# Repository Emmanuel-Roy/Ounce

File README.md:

# Ounce

Play your Nintendo Switch from anywhere. Four Picos each appear to the Switch as
a real Switch Pro Controller, a fifth drives them over SPI, and a Windows client
turns your keyboard and USB pads into those four players while showing the
Switch's video in the same window.

```
keyboard / pads -> Windows client -> USB serial -> Pico 2 W master
                                                        |  SPI
                                          +------+------+------+------+
                                        Pico   Pico   Pico   Pico   -> Switch USB
                                       player1 player2 player3 player4
```

> **The artwork is AI-generated.** The banner, logo and app icon all came out of
> an image model — this is a hobby project and I could not afford to pay an
> artist for it. Everything in [`Ounce-Client/Graphics/`](Ounce-Client/Graphics/)
> is that; the photos of the board and the wiring are real. Artists welcome —
> open an issue.

## Parts

| Qty | Part | Purpose |
| --- | --- | --- |
| 1 | **Raspberry Pi Pico 2 W** (RP2350) | Master |
| 4 | **Raspberry Pi Pico 1** (RP2040) | Servants — one per player |
| 5 | Micro-USB cables | 4 for servants -> Switch (powered hub into the dock), 1 for master -> PC (power + serial) |
| 1 | **Elgato capture card** (4K S or similar) | Switch video in the client window |
| 1 | **Ounce PCB** or breadboard + jumpers | SPI bus and common ground |

Capture card is optional — run with `--no-preview` for input only.

## Layout

```
bin/
├── firmware/      OunceMaster.uf2, OunceServant.uf2   <-- flash these
├── client/        OunceClient/ - the app, no Python needed
└── pcb/           Ounce-PCB-fab.zip - gerbers + drill, ready to order
Ounce-Client/      Windows client: test_bridge.py, wiring_test.py, build_exe.bat
└── Graphics/      AI-generated logo, icon and banner - all of it, see its README
Ounce-Hardware/    master-firmware/, servant-firmware/, pcb/, pico-sdk/
```

## Wiring

SCK and MOSI are **shared** by all four servants. CS and MISO are **one per
servant** — an RP2040 slave does not release MISO when deselected, so four on
one wire would fight.

**Master (Pico 2 W)**

| Signal | GPIO | Pin | To |
| --- | --- | --- | --- |
| SCK | GP18 | 24 | SCK on all servants |
| MOSI | GP19 | 25 | MOSI (GP16) on all servants |
| CS 0–3 | GP21, GP22, GP26, GP27 | 27, 29, 31, 32 | CS on servant 0, 1, 2, 3 |
| MISO 0–3 | GP0, GP4, GP16, GP20 | 1, 6, 21, 26 | MISO from servant 0, 1, 2, 3 |
| GND | GND | 38 | GND (pin 38) on every servant |

**Each servant (Pico 1)** — identical for all four:

| Signal | GPIO | Pin | To |
| --- | --- | --- | --- |
| MOSI in | GP16 | 21 | master GP19 |
| CS | GP17 | 22 | that servant's own CS pin |
| SCK | GP18 | 24 | master GP18 |
| MISO out | GP19 | 25 | that servant's own MISO pin |
| GND | GND | 38 | master GND (pin 38) |

**Every board must share a ground with the master** — without it you get
intermittent garbage rather than a clean failure. Bus is 4 MHz, SPI mode 1.
Servants are numbered purely by which CS pin they are wired to, so any Pico
works in any slot.

Breadboard and jumpers work fine — this is the build the firmware was developed
against, and it holds 94–100% packet delivery at 4 MHz:

The PCB is the same eleven nets, tidier.

Verify before going further:

```bash
python Ounce-Client/wiring_test.py            # PASS/FAIL per slot
python Ounce-Client/wiring_test.py --identify # drive one slot at a time
python Ounce-Client/wiring_test.py --map      # slot -> board -> Windows USB device
```

SPI slot order and USB enumeration order are unrelated — slot 2 is just "the
board on CS GP26" and may appear third or fourth in Windows.

## Flashing

Prebuilt images are in `bin/` — no build needed.

| Board | Hold BOOTSEL, plug in, drive appears | Drag on |
| --- | --- | --- |
| Servants (×4) | `RPI-RP2` | `bin/firmware/OunceServant.uf2` |
| Master | `RP2350` | `bin/firmware/OunceMaster.uf2` |

All four servants get the **same** file; each learns its player number from its
CS pin.

The servants ask the Switch to poll them every **1 ms**, not the 8 ms a real Pro
Controller reports — that interval was over half of Ounce's total input latency.
If a servant will not enumerate on the console, that non-standard `bInterval` in
`SwitchProDescriptors.h` is the first thing to put back to `0x08`.

## Building

```bash
git clone --recursive https://github.com/Emmanuel-Roy/Ounce.git
```

Already cloned? `git submodule update --init --recursive`.

**Master firmware** — needs CMake, a make tool and `arm-none-eabi-gcc` (the [Pico
Windows installer](https://www.raspberrypi.com/documentation/microcontrollers/c_sdk.html)
has all three):

```bash
cd Ounce-Hardware/master-firmware
cmake -B build -DPICO_SDK_PATH=../pico-sdk
cmake --build build
```

Add `-G Ninja` or `-G "MinGW Makefiles"` if CMake does not pick a generator on
its own. Output is `build/OunceMaster.uf2`.

**Servant firmware** (`SKIP_WEBBUILD` avoids needing Node/npm for GP2040-CE's
unused web configurator):

```bash
cd Ounce-Hardware/servant-firmware/GP2040-CE-SPI
cmake -B build -DSKIP_WEBBUILD=ON -DPICO_SDK_PATH=../../pico-sdk
cmake --build build
```

Output is `build/OunceServant.uf2`. Both firmwares use the vendored SDK, which
is pinned to **2.2.0** because that is what GP2040-CE builds against — on 2.3.0
the servant fails to link, with mbedtls calling PSA crypto functions that its
config leaves out.

If that build dies in **picotool** rather than in the firmware (`No rule to make
target ...compiler_depend.make` under `enc_bootloader_mbedtls`), the SDK is
building picotool from source and failing at it — seen with the MinGW Makefiles
generator. Point CMake at one that already exists instead:

```bash
cmake -B build -DSKIP_WEBBUILD=ON -DPICO_SDK_PATH=../../pico-sdk \
      -Dpicotool_DIR=<some-existing-build>/_deps/picotool
```

That directory is the one holding `picotoolConfig.cmake`, not `picotool-build/`.

**Client:**

```bash
pip install -r Ounce-Client/requirements.txt
python Ounce-Client/test_bridge.py
```

`python-vlc` is only the binding — also install VLC itself, at the same
bit-width as your Python, or video will not start.

`Ounce-Client\build_exe.bat` rebuilds `bin\client\OunceClient\`. It uses `--onedir`
deliberately: a onefile build relaunches itself as a child process, and Steam
Input only instruments the process Steam launched. Keep the folder together —
the exe needs `_internal\` beside it. The exe icon and the window icon both come
from `Graphics/icon.png` beside it —
[`Ounce-Client/Graphics/README.md`](Ounce-Client/Graphics/README.md) has the
one-liner that regenerates them.

## Running

Run with no arguments and it asks what drives each player:

```text
   1) PS5 Controller     k) Keyboard     d) Disabled

  Controller 1 (slot 0) : 1
  Controller 2 (slot 1) : k
```

Ounce's own servants are filtered out of the list. Only assigned slots are
enabled. To skip the prompt:

```bash
python test_bridge.py --assign all=keyboard
python test_bridge.py --assign 0=pad:DualSense --assign 1,2,3=keyboard
python test_bridge.py --list-controllers
```

`SLOT` is `0`–`3`, a comma list, or `all`; `SOURCE` is `keyboard` or
`pad:<index|name>` (prefer names — indices shift when devices are replugged).

A pad and the keyboard can drive the same player at once. Each player's menu
lists the controllers first, then how much keyboard rides along with it:

| Keyboard | Player gets |
| --- | --- |
| **Full keyboard** | every input, merged with the pad |
| **Home / Capture only** | just those two keys; the rest of the keyboard is ignored |
| **No keyboard** | the pad alone |

**Home / Capture only** is the useful one for a Steam Controller, which has no
Home or Capture button: you get those two without WASD also grabbing the stick
out from under the pad. The keyboard setting belongs to the player rather than
the pad, so changing which controller is assigned keeps it.

On the Switch: **System Settings → Controllers and Sensors → Pro Controller
Wired Communication → ON**.

**Video** — the window opens by default at **1440p60 raw** (`--no-window` for a
headless console bridge). `--list-modes` shows what your card offers,
`--capture-mode 3840x2160` to override. **F11** toggles borderless fullscreen.

1440p raw is the default because it is the highest mode that actually holds 60.
Measured on an RX 9070 XT / Ryzen 7 7700X:

| Mode | Frame rate | Dropped |
| --- | --- | --- |
| 2560×1440@60 nv12 | **59.0 / 60** | 1 |
| 3840×2160@60 mjpeg | 40.6 / 60 | 129 |
| 2560×1440@144 mjpeg | 90.8 / 144 | 386 |

4K60 is MJPEG only — the card caps raw at 4K30 — and MJPEG costs a CPU decode
plus a software colour conversion on every frame. Neither GPU decode nor more
decoder threads helps: AMD and NVIDIA have no MJPEG hardware decoder, and
raising `--avcodec-threads` past 4 makes it worse. Raw skips both steps, so the
frames go straight to the GPU.

A mode must be requested explicitly or DirectShow hands out 640×480. The card's
HDMI passthrough never reaches the PC, so only the capture path can feed the
window.

**Video latency.** If you play off this window rather than off the card's HDMI
passthrough, the picture — not the controller — is what you feel. The input path
is about 1.7 ms end to end, so anything the capture path buffers dwarfs it.

Audio is therefore split out of VLC by default, and `--capture-latency` defaults
to **20 ms** of *video* buffering. The buffer only ever existed for the audio
output, which crackles when starved; with the sound on its own pipe the picture
does not have to pay for it.

| Flag | Effect |
| --- | --- |
| `--capture-latency N` | Video buffer in ms. Lower until the picture stops improving — what is left below that is the card's own pipeline, which no setting here can shorten |
| `--audio-latency N` | How far ahead the audio pipe queues, default 100 ms. Delays only the sound, so raise it if you hear crackling |
| `--no-split-audio` | Put audio back through VLC. Then `--capture-latency` buffers sound too, and 20 will crackle — use 100–200 |

Both are also in the dropdown under **latency**, so they can be tuned by ear
while the game is running rather than by restarting with a different flag. The
audio row only appears when audio is on its own pipe — with `--no-split-audio`
the video buffer *is* the audio buffer and a second setting would do nothing.
Changing the video buffer restarts the stream, so it is refused mid-recording.

Crackling is the audio output running dry, and it is fixed with the audio
buffer, never the video one. The two are independent now: sound runs ~100 ms
behind the picture, which is the forgiving direction — broadcast practice
tolerates about 125 ms of audio lag against roughly 45 ms of lead.

Run from a console and the client reports what it actually got — the device
buffer it was given, the cushion primed into it, and anything ffmpeg says about
the capture side. Capture-side and output-side dropouts sound identical and
need opposite fixes, so it is worth reading which one you have.

Recordings take their audio from VLC either way, so `capture.avi` keeps its
sound; latency rises for the length of a take and drops again on stop. If
ffmpeg or `sounddevice` is missing the client says so and keeps audio in VLC
rather than playing none.

## Shaders (mpv backend)

`--video-backend mpv` draws the card on the GPU straight into the window, the
same as VLC — but mpv has a **programmable shader stage**, and VLC has none.
That is the only place in this client where a GLSL pass can run between decode
and display, which makes it the only way to attack aliasing that was baked into
the signal before the card ever saw it.

This matters when the game's internal render resolution is below what the
console outputs. Anime4K's `Restore_CNN` shaders were built for exactly that —
material rendered small and scaled up — and unlike an upscaler they do useful
work even at 1:1, so they apply on a 1440p feed shown on a 1440p display.

```bash
OunceClient.exe --video-backend mpv --shader Restore_CNN_M
OunceClient.exe --list-shaders          # what's in your mpv shaders folder
```

| Flag | Effect |
| --- | --- |
| `--video-backend mpv` | GPU rendering with a shader stage |
| `--shader NAME\|PATH` | A `.glsl` by full path, or by name — matched loosely, so `restore_cnn_m` finds `Anime4K_Restore_CNN_M` |
| `--scaler NAME` | mpv's kernel, default `ewa_lanczossharp`. Only acts when the window is a different size from the source |
| `--dscale NAME` | Supersampling kernel — see below. Default `mitchell` |
| `--mpv-path PATH` | Where `mpv.exe` is, if not on PATH |

### Supersampling

Shrinking a 1440p feed into a smaller window **is** supersampling, and mpv does
it correctly with no flags at all: `correct-downscaling` (enough taps to average
the detail away instead of point-sampling it into aliasing) and
`linear-downscaling` (average in linear light, so edges don't darken) are both
on by default — verified by asking a running player, not by reading the docs.

So on this backend supersampling is already on. What's left to choose is the
kernel, `--dscale`: `mitchell` (default here — softer, loses stairsteps) or
`hermite` (mpv's own default — sharper, keeps them). It's on the toolbar as
**Supersample**, and it applies live.

**It only works while the window is smaller than the source.** At 1:1 there is
nothing to average and the kernel sits idle no matter what it's set to. The
toolbar row says which of the two you're in rather than just naming the kernel:

```
Supersample :  mitchell   (active, 2560 -> 960 across, 2.67x)
Supersample :  mitchell   (idle: 1:1 at 2560 - nothing to supersample)
```

That means a 1440p feed shown fullscreen on a 1440p display gets no
supersampling — there are exactly as many source pixels as screen pixels. To get
it there, the source has to carry more pixels than the display: capture at 4K and
show at 1440p, if the console will output 4K. Otherwise supersampling is a
windowed-play benefit, which is why shrinking the window looks better.

Shader and scaler are on the toolbar under **picture** and apply **live** — mpv
swaps them on a running stream, so unlike every other setting here nothing
restarts and nothing is refused mid-recording.

**mpv is not bundled.** A static `mpv.exe` is ~117 MB, which has no business in
a git repository — GitHub refuses files that size. Install mpv and put it on
PATH, exactly as VLC is already a separate install. Shaders are read from
`%APPDATA%\mpv\shaders`; none are shipped, since Anime4K has its own licence and
anyone using mpv already curates that folder.

Your own `mpv.conf` is deliberately **not** inherited. A config tuned for
watching video is the wrong one for playing a game through — `interpolation` and
`video-sync=display-resample` each add frames of latency. Shaders still work,
because they are passed by full path.

Recording on this backend uses mpv's `stream-record` into `capture.mkv`, toggled
live. That is strictly better than the VLC path, which has to restart the stream
to start or stop a take.

## Upscaler

The card sends 1440p, but a game rendering below that and letting the console
scale up puts the stairsteps into the signal *before* the card sees them. No
filter puts back detail that was never drawn.

What does work is the thing you notice by accident: **shrinking the window makes
the picture look good.** A downscale averages each stairstep away — that is
supersampling, and it is the strongest antialiasing there is. The upscaler
reproduces it at any window size: resample down to a render height, then back up
to the window, both passes in linear light.

| Flag | Effect |
| --- | --- |
| `--upscale off\|fast\|aa` | `aa` is the shrink-and-rebuild described above. `fast` is one good-kernel resample with no shrink. Default `off` |
| `--render-height H` | How far `aa` shrinks first. Lower is stronger antialiasing and a softer picture; `0` skips the shrink. Default 720 |
| `--sharpen S` | Contrast-adaptive sharpening afterwards, 0.0–1.0, to put back the bite the resample costs. Default 0.4 |

All three are in the dropdown under **picture**, so you can tune by eye on the
game you are actually playing. The rows only appear on the ffmpeg backend —
**this needs `--video-backend ffmpeg`.** The VLC backend hands frames straight
to the GPU and never lets a filter chain near them, which is exactly why it is
fast; there is nowhere in it to put an upscaler.

Measured here at 1440p60 in, on synthetic input: the `aa` chain sustains ~94 fps
to a 1440p window and ~175 fps to 1080p, against the 60 needed. The filters are
not the constraint. Latency is untested on hardware — the ffmpeg path adds a
pipe hop the VLC path does not have, so check it feels right before committing
to it for play.

Two things this also fixed on the ffmpeg path, which were costing picture
quality whether or not the upscaler is on:

- It scaled to a fixed 960x540 and then had pygame stretch that back up to the
  window — two lossy resamples, neither at the size being displayed. The pipe
  now carries the window size, so the picture is resampled once.
- Raw DirectShow frames carry no colour tag, so swscale assumed bt601 at every
  resolution. On an HD feed that is the wrong matrix, worth about 4 code values.
  Every chain now tags bt709 at HD and bt601 below it.

## Recording

**Rec** on the toolbar starts and stops a recording. Each one is a folder in
`bin\recordings\`, named for when it started and how long it ran
(`2026-08-14_21-30-05_3m12s`), containing:

```
capture.avi        video + audio from the card
controller1.csv    what was sent to player 1
controller3.csv    ...one file per player that was actually driven
```

The CSVs are `t_ms,buttons,lx,ly,rx,ry,aux`, timed from the start of the
recording so they line up with the video beside them.

Frames are written in the codec they arrive in — no re-encoding, since
compressing 4K60 in software would not keep up. In an MJPEG mode that is a
normal-sized file; in a **raw** mode it is roughly 180 MB/s, and the client
warns you before starting one. Capture settings cannot be changed mid-recording
because applying them restarts the stream, which would truncate the file.

## Steam Controller (Steam Input)

**A Steam Controller only works if you add `OunceClient.exe` to Steam and launch
it from there.** Outside Steam it is a keyboard/mouse device with no gamepad for
anything to detect, and Steam Input only turns it into one for processes **Steam
launches itself** — running the exe directly will never see it.

1. **Steam → Games → Add a Non-Steam Game → Browse** →
   `bin\client\OunceClient\OunceClient.exe`
2. Right-click → **Properties → Controller → Enable Steam Input**
3. **Edit Layout** → bind sticks to **Joystick Move**, *not* D-Pad
4. Launch from Steam, then **click the window once** — Steam only leaves
   Desktop mode for a focused window, or the pad stays in mouse mode

Steam shows a blank grid tile for non-Steam games. Right-click → **Manage → Set
custom artwork** and point it at `Ounce-Client/Graphics/library.png` (the
600×900 portrait) and `Ounce-Client/Graphics/banner.jpg` (the wide header).

Sticks bound to D-Pad are cut to eight directions before Ounce sees them and the
analog range cannot be recovered. Set Launch Options to `--probe` to check:
motion should move `AXES`, not `HATS`.

The client sets `SDL_JOYSTICK_HIDAPI_STEAM` for you — `0` under Steam, `1`
otherwise. Left at SDL's default under Steam, SDL would talk to the pad
directly over HID and bypass Steam Input entirely, so the layout you configured
would silently do nothing.

**Parsec** controllers arrive as ordinary XInput pads, so they need none of the
above — they appear in the input list by themselves and can be assigned to a
slot like any other controller. The name will be a generic XInput one rather
than whatever the remote player is actually holding, so with several connected,
`--list-controllers` and the assignment order are what tell them apart.

## Remapping controls

Dropdown at the top of the window → **Remap keyboard controls…**. Click an
input, press a key. **Esc** cancels, **reset all** restores defaults. Rebinding
a key in use takes it from its previous owner, and changes apply instantly to
every player on the keyboard.

Remaps are saved to `%APPDATA%\Ounce\keymap.json` as you make them and reload
on the next launch, so this only has to be done once. Deleting that file
restores the defaults below.

| Input | Key | Input | Key | Input | Key |
| --- | --- | --- | --- | --- | --- |
| L-Stick U/D/L/R | `W` `S` `A` `D` | D-Pad | arrows | X / Y / B / A | `I` `J` `K` `L` |
| R-Stick U/D/L/R | `8` `0` `7` `9` | L / R | `U` `O` | ZL / ZR | `Y` `P` |
| L3 / R3 | `Z` `X` | + / − | `N` `M` | Home / Capture | `H` `C` |

The same dropdown holds the video device, capture mode (raw vs compressed) and
each player's input source. For pad mappings or a saved keyboard layout:

```bash
python test_bridge.py --dump-config mymap.json
python test_bridge.py --config mymap.json
```

## Troubleshooting

| Symptom | Cause |
| --- | --- |
| One slot fails wiring test | That slot's CS or MISO — SCK/MOSI faults break *all* slots |
| All slots fail | Missing common ground, or SCK/MOSI disconnected |
| Enumerates on Switch but does nothing | Wired communication off in Switch settings |
| Steam Controller acts as a mouse | Window not focused, or Steam Input not enabled |
| Sticks give only 8 directions | Steam layout has them on D-Pad |
| Video is 640×480 | No capture mode requested |
| Video will not start | VLC missing, or wrong bit-width for your Python |

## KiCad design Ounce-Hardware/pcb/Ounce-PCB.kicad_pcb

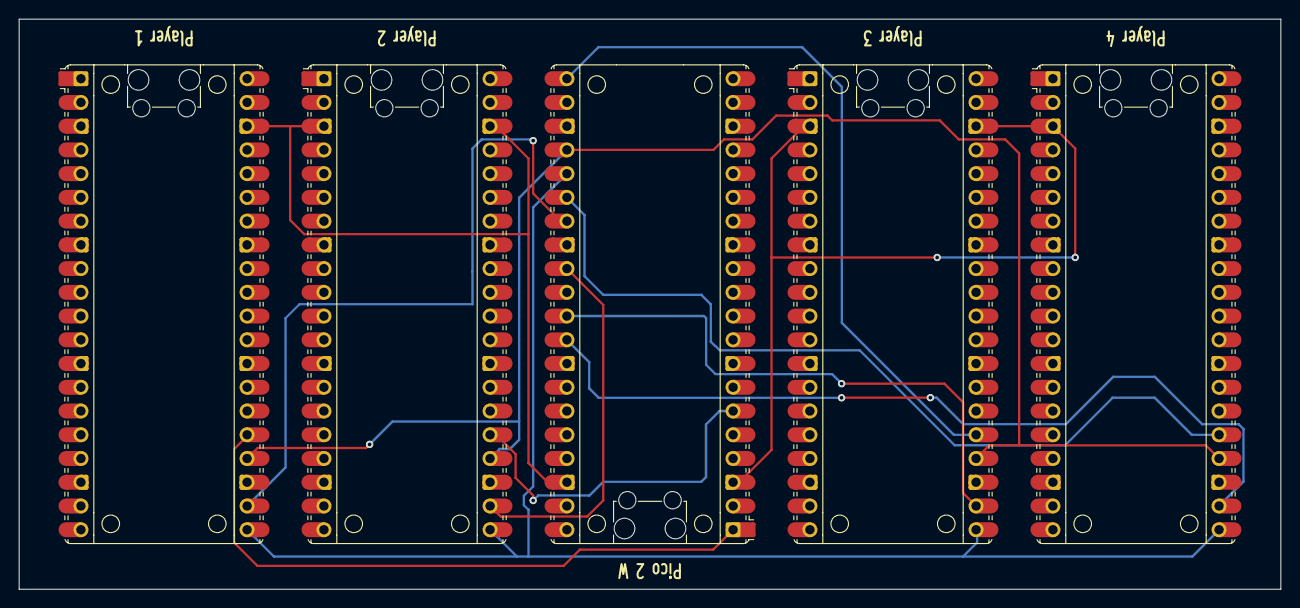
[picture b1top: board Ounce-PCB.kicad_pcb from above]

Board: 2 copper layers, 135.0 x 61.0 mm, 5 parts (0 on the bottom side), 11 nets.

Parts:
U1: RaspberryPi_Pico2_W; RaspberryPi_Pico_Common
U2, U3, U4, U5: RaspberryPi_Pico; RaspberryPi_Pico_Common

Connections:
GND: U1.3 (GND), U1.38 (GND), U2.3 (GND), U2.38 (GND), U3.3 (GND), U3.38 (GND), U4.3 (GND), U4.38 (GND), U5.3 (GND), U5.38 (GND)
SPI0_CS0: U1.27 (GPIO21), U2.22 (GPIO17)
SPI0_CS1: U1.29 (GPIO22), U3.22 (GPIO17)
SPI0_CS2: U1.31 (GPIO26_ADC0), U4.22 (GPIO17)
SPI0_CS3: U1.32 (GPIO27_ADC1), U5.22 (GPIO17)
SPI0_MISO0: U1.1 (GPIO0), U2.25 (GPIO19)
SPI0_MISO1: U1.6 (GPIO4), U3.25 (GPIO19)
SPI0_MISO2: U1.21 (GPIO16), U4.25 (GPIO19)
SPI0_MISO3: U1.26 (GPIO20), U5.25 (GPIO19)
SPI0_MOSI: U1.25 (GPIO19), U2.21 (GPIO16), U3.21 (GPIO16), U4.21 (GPIO16), U5.21 (GPIO16)
SPI0_SCK: U1.24 (GPIO18), U2.24 (GPIO18), U3.24 (GPIO18), U4.24 (GPIO18), U5.24 (GPIO18)

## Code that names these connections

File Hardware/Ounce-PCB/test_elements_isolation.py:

import subprocess
import re
import uuid

sch_path = r'Z:\Code\Github\Ounce\Hardware\Ounce-PCB\Ounce-PCB.kicad_sch'
test_pdf = r'Z:\Code\Github\Ounce\Hardware\Ounce-PCB\test.pdf'
kicad_cli = r'C:\Program Files\KiCad\7.0\bin\kicad-cli.exe'

with open(r'Z:\Code\Github\Ounce\Hardware\Ounce-PCB\ki-lime-pi-to-go\MCU_Module_RaspberryPi_Pico.kicad_sym', 'r', encoding='utf-8') as f:
    sym_file = f.read()

def extract_symbol(text, sym_name):
    target = f'(symbol "{sym_name}"'
    idx = text.find(target)
    if idx == -1:
        return ""
    count = 0
    start = idx
    for i in range(idx, len(text)):
        if text[i] == '(':
            count += 1
        elif text[i] == ')':
            count -= 1
            if count == 0:
                return text[start:i+1]
    return ""

pico = extract_symbol(sym_file, "RaspberryPi_Pico")
picow = extract_symbol(sym_file, "RaspberryPi_Pico_W")

def convert_to_kicad7_lib_symbol(txt):
    txt = re.sub(r'\s*\(do_not_autoplace\s+[^)]+\)', '', txt)
    txt = re.sub(r'\s*\(in_bom\s+[^)]+\)', '', txt)
    txt = re.sub(r'\s*\(on_board\s+[^)]+\)', '', txt)
    txt = re.sub(r'\s*\(property "ki_[^"]*"[\s\S]*?\n\s*\)', '', txt)
    txt = re.sub(r'\s*\(alternate\s+[^)]+\)', '', txt)
    txt = re.sub(r'(\(pin\s+[^)]+\))\s+hide', r'\1', txt)
    txt = txt.replace('(effects (font (size 1.27 1.27))) hide', '(effects (font (size 1.27 1.27)) hide)')
    return txt

pico_clean = convert_to_kicad7_lib_symbol(pico)
picow_clean = convert_to_kicad7_lib_symbol(picow)

symbols_info = [
    ('U1', 'RaspberryPi_Pico_W', 'RaspberryPi_Pico_W', 50.8, 63.5),
    ('U2', 'RaspberryPi_Pico', 'RaspberryPi_Pico', 114.3, 63.5),
    ('U3', 'RaspberryPi_Pico', 'RaspberryPi_Pico', 177.8, 63.5),
    ('U4', 'RaspberryPi_Pico', 'RaspberryPi_Pico', 241.3, 63.5),
    ('U5', 'RaspberryPi_Pico', 'RaspberryPi_Pico', 304.8, 63.5),
]

symbol_elements = []
symbol_instances = []

for ref, lib_id, val, x, y in symbols_info:
    u = str(uuid.uuid4())
    symbol_instances.append(f"""    (path "/{u}"
      (reference "{ref}")
      (unit 1)
    )""")
    symbol_elements.append(f"""  (symbol (lib_id "{lib_id}") (at {x:.2f} {y:.2f} 0) (unit 1)
    (in_bom yes) (on_board yes) (uuid "{u}")
    (property "Reference" "{ref}" (at {x:.2f} {y-40.64:.2f} 0)
      (effects (font (size 1.27 1.27)) (justify left))
    )
    (property "Value" "{val}" (at {x:.2f} {y-38.1:.2f} 0)
      (effects (font (size 1.27 1.27)) (justify left))
    )
    (property "Footprint" "Module_RaspberryPi_Pico:RaspberryPi_Pico_Common" (at {x:.2f} {y+40.64:.2f} 0)
      (effects (font (size 1.27 1.27)) (justify left) hide)
    )
  )""")

global_labels = []
def add_label(name, x, y, shape="bidirectional", angle=0):
    u = str(uuid.uuid4())
    global_labels.append(f"""  (global_label "{name}" (shape {shape}) (at {x:.2f} {y:.2f} {angle})
    (effects (font (size 1.27 1.27)) (justify left))
    (uuid "{u}")
  )""")

# Labels for U1 (Master)
add_label("SPI0_SCK", 73.66, 53.34, shape="input")
add_label("SPI0_MOSI", 73.66, 54.61, shape="input")
add_label("SPI0_CS0", 73.66, 57.15, shape="input")
add_label("SPI0_CS1", 73.66, 59.69, shape="input")
add_label("SPI0_CS2", 73.66, 62.23, shape="input")
add_label("SPI0_CS3", 73.66, 72.39, shape="input")
add_label("GND", 50.80, 101.60, shape="passive", angle=270)

# Labels for U2 (Slave 0)
add_label("SPI0_SCK", 137.16, 53.34, shape="input")
add_label("SPI0_MOSI", 137.16, 55.88, shape="input")
add_label("SPI0_CS0", 137.16, 58.42, shape="input")
add_label("GND", 114.30, 101.60, shape="passive", angle=270)

# Labels for U3 (Slave 1)
add_label("SPI0_SCK", 200.66, 53.34, shape="input")
add_label("SPI0_MOSI", 200.66, 55.88, shape="input")
add_label("SPI0_CS1", 200.66, 58.42, shape="input")
add_label("GND", 177.80, 101.60, shape="passive", angle=270)

# Labels for U4 (Slave 2)
add_label("SPI0_SCK", 264.16, 53.34, shape="input")
add_label("SPI0_MOSI", 264.16, 55.88, shape="input")
add_label("SPI0_CS2", 264.16, 58.42, shape="input")
add_label("GND", 241.30, 101.60, shape="passive", angle=270)

# Labels for U5 (Slave 3)
add_label("SPI0_SCK", 327.66, 53.34, shape="input")
add_label("SPI0_MOSI", 327.66, 55.88, shape="input")
add_label("SPI0_CS3", 327.66, 58.42, shape="input")
add_label("GND", 304.80, 101.60, shape="passive", angle=270)

full_sch = f"""(kicad_sch (version 20230121) (generator eeschema) (generator_version "7.0")
  (uuid "64149908-1f33-4118-b113-679e16cf28e6")
  (paper "A4")
  (lib_symbols
{pico_clean}
{picow_clean}
  )
{chr(10).join(symbol_elements)}
{chr(10).join(global_labels)}
  (sheet_instances
    (path "/" (page "1"))
  )
  (symbol_instances
{chr(10).join(symbol_instances)}
  )
)
"""

with open(sch_path, 'w', encoding='utf-8') as f:
    f.write(full_sch)

res = subprocess.run([kicad_cli, 'sch', 'export', 'pdf', '-o', test_pdf, sch_path], capture_output=True, text=True)
print("Clean short lib_id matching lib_symbols exit code:", res.returncode)
print("stdout:", res.stdout)
print("stderr:", res.stderr)
